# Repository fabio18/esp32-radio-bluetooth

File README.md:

# ESP32 Kindlelaser Max 260W — Metal Cutting Controller

Painel de controle **touch screen** para máquina de corte a laser CO2 **Kindlelaser Max 130W/260W**.
Interface visual industrial com **presets de corte de metal**, monitoramento de segurança e LEDs de status.

## Funcionalidades

- **Controle de potência** PWM (5-99%) com display em Watts
- **Controle de velocidade** de corte (1-80 mm/s)
- **12 presets de material** (Aço Carbono, Inox, Alumínio) com espessuras
- **Monitoramento de segurança**: fluxo de água, tampa, temperatura, E-stop
- **Pulso de teste** para alinhamento do laser
- **Ar comprimido** e **exaustor** controlados pela tela
- **LED WS2812B** para indicação visual de status da máquina
- **Interface touch** — sem botões físicos

## Componentes

| Componente | Descrição |
|---|---|
| **ESP32 DevKit** | Microcontrolador com Wi-Fi (para monitoramento futuro) |
| **ILI9341 TFT 2.4"** | Display 240x320 **com touch XPT2046** |
| **WS2812B** | Fita LED (30 LEDs) para status da máquina |
| **Optoacoplador** | 4N35 ou PC817 — isolamento ESP32 ↔ PSU laser |
| **Conversor de nível** | 3.3V → 5V para sinal PWM |
| **Relé 5V (2ch)** | Para ar comprimido e exaustor |
| **Sensor de fluxo** | Fluxo de água (tipo YF-S201) |
| **NTC 10kΩ** | Sensor de temperatura da água |
| **Botão E-STOP** | Emergência (NC - normalmente fechado) |
| **Chave de tampa** | Microswitch na porta da máquina |

## Layout da Tela Touch

```
┌─────────────────────────────┐
│ KINDLELASER 260W    [STATUS]│  Header
├─────────────────────────────┤
│ MAT: Aco 2.0mm        [O2] │  Preset de material
├─────────────────────────────┤
│   POTENCIA: 95%  (247W)    │  Potência (grande)
│   VELOCIDADE: 12 mm/s      │  Velocidade
├─────────────────────────────┤
│ [POT-] [POT+] [SPD-] [SPD+]│  Controles pot/velocidade
│ [<MAT]  [PULSO]  [MAT>]   │  Material presets
│ [AR]  [EXAUST]  [E-STOP]  │  Auxiliares
│ [═══ LASER ON/OFF ════════]│  Botão principal
├─────────────────────────────┤
│ ████████████████░░░░  95%  │  Barra de potência
├─────────────────────────────┤
│ H2O:OK LID:OK 25°C SEGURO │  Status de segurança
└─────────────────────────────┘
```

## Diagrama de Conexões

### ESP32 → PSU Laser (Kindlelaser Max 260W)

```
ESP32 GPIO 25 (PWM) ──[330Ω]──→ Conversor 3.3V→5V ──→ PSU "IN" (0-5V potência)
ESP32 GPIO 26       ──[1kΩ]──→ Optoacoplador 4N35 ──→ PSU "L-ON" (Laser Enable)
                                 (isolamento galvânico obrigatório!)
```

### ESP32 → Relés de Controle

```
ESP32 GPIO 14  ──→ Relé CH1 ──→ Solenoide ar comprimido (24V)
ESP32 GPIO 12  ──→ Relé CH2 ──→ Exaustor/ventilação (220V)
```

### ESP32 ← Sensores de Segurança

```
Sensor de Fluxo (YF-S201)  ──→ GPIO 33 (INPUT_PULLUP)
Chave de Tampa (NC)         ──→ GPIO 32 (INPUT_PULLUP)
Botão E-STOP (NC)           ──→ GPIO 39 (VN - INPUT)
NTC 10kΩ (divisor)          ──→ GPIO 35 (ADC)
```

### Circuito NTC Temperatura

```
3.3V ──[10kΩ]──┬──[NTC 10kΩ]── GND
               │
               └── GPIO 35 (ADC)
```

### ILI9341 TFT + Touch → ESP32 (SPI)

```
ILI9341      ESP32         Função
───────      ─────         ──────
MOSI   ───── GPIO 23       SPI Data (compartilhado)
MISO   ───── GPIO 19       SPI Data (compartilhado)
SCK    ───── GPIO 18       SPI Clock (compartilhado)
CS     ───── GPIO 15       Chip Select Display
DC     ───── GPIO  2       Data/Command
RST    ───── GPIO  4       Reset
LED    ───── 3.3V          Backlight
T_CS   ───── GPIO 27       Chip Select Touch
T_IRQ  ───── GPIO 34       Touch Interrupt (opcional)
VCC    ───── 3.3V
GND    ───── GND
```

### WS2812B LED Strip

```
WS2812B      ESP32
───────      ─────
DIN    ───── GPIO 13       Data (com resistor 330Ω)
VCC    ───── 5V            Fonte externa
GND    ───── GND           Compartilhado
```

### Diagrama Completo

```
                    ┌─────────────────────┐
                    │     ESP32 DevKit     │
                    │                     │
  PSU Laser ──PWM──┤ GPIO25 (PWM)        │── 20kHz → 0-5V potência
  (Kindlelaser)     │ GPIO26 (ENABLE)     │── Optoacoplador → L-ON
                    │                     │
  ILI9341 ───SPI──┤ GPIO23 (MOSI)       │── compartilhado
  (Display)        │ GPIO19 (MISO)       │── com touch
                   │ GPIO18 (SCK)        │── XPT2046
                   │ GPIO15 (CS Display) │
                   │ GPIO2  (DC)         │
                   │ GPIO4  (RST)        │
                   │                     │
  XPT2046 ────────┤ GPIO27 (CS Touch)   │
  (Touch)          │                     │
                   │                     │
  Ar Comprimido ──┤ GPIO14 (Relé)       │── Solenoide 24V
  Exaustor ───────┤ GPIO12 (Relé)       │── Ventilação 220V
                   │                     │
  WS2812B ────────┤ GPIO13 (LED Data)   │
  (Status LEDs)    │                     │
                   │                     │
  Sensor Fluxo  ──┤ GPIO33 (INPUT)      │── Água OK?
  Chave Tampa  ───┤ GPIO32 (INPUT)      │── Tampa fechada?
  E-STOP  ────────┤ GPIO39 (INPUT)      │── Emergência?
  NTC Temp  ──ADC─┤ GPIO35 (ADC)        │── Temperatura água
                   │                     │
                   └─────────────────────┘
```

---

## Presets de Corte de Metal (Kindlelaser 260W)

| # | Material | Espessura | Potência | Velocidade | Gás |
|---|---|---|---|---|---|
| 1 | Aço Carbono | 0.5mm | 70% | 30 mm/s | O₂ |
| 2 | Aço Carbono | 1.0mm | 85% | 20 mm/s | O₂ |
| 3 | Aço Carbono | 1.5mm | 92% | 15 mm/s | O₂ |
| 4 | Aço Carbono | 2.0mm | 95% | 12 mm/s | O₂ |
| 5 | Aço Carbono | 3.0mm | 99% | 8 mm/s | O₂ |
| 6 | Inox | 0.5mm | 75% | 25 mm/s | N₂ |
| 7 | Inox | 1.0mm | 90% | 15 mm/s | N₂ |
| 8 | Inox | 1.5mm | 95% | 10 mm/s | N₂ |
| 9 | Inox | 2.0mm | 99% | 6 mm/s | N₂ |
| 10 | Alumínio | 0.5mm | 80% | 20 mm/s | N₂ |
| 11 | Alumínio | 1.0mm | 92% | 12 mm/s | N₂ |
| 12 | Alumínio | 1.5mm | 99% | 7 mm/s | N₂ |

> **Nota:** Estes valores são pontos de partida. Ajuste conforme o estado do tubo, lente e condições do material. A Kindlelaser 130W corta até ~2mm de aço; a 260W até ~3mm.

---

## Sistema de Segurança

O sistema implementa **4 camadas de segurança**:

| Sensor | Condição para operar | Ação se falhar |
|---|---|---|
| **Fluxo de água** | Sensor detecta fluxo (LOW) | Desliga laser imediatamente |
| **Tampa** | Microswitch fechado (LOW) | Desliga laser imediatamente |
| **E-STOP** | Botão não pressionado (HIGH) | Desliga TUDO (emergency stop) |
| **Temperatura** | < 35°C | Desliga laser + aviso |

Adicionalmente:
- **Tempo máximo de corte contínuo**: 5 minutos → pausa obrigatória
- **Potência máxima limitada**: 99% (protege vida útil do tubo)
- **Ar comprimido obrigatório**: não pode ser desligado durante corte
- **Exaustor automático**: liga junto com o laser

---

## Indicação LED (WS2812B)

| Status | Efeito LED | Significado |
|---|---|---|
| **IDLE** | Azul pulsante (respiração) | Máquina em espera |
| **PRONTO** | Verde fixo | Segurança OK, pronto para cortar |
| **CORTANDO** | Vermelho pulsante rápido | Laser ativo! |
| **AVISO** | Amarelo piscante | Temperatura alta ou pausa |
| **ERRO** | Vermelho piscante | Falha de segurança |
| **RESFRIANDO** | Azul gradiente | Aguardando resfriamento |

---

## Como Compilar e Gravar

### PlatformIO (recomendado)

```bash
# Compilar
pio run

# Gravar no ESP32
pio run --target upload

# Monitor Serial
pio device monitor
```

### Arduino IDE

1. Instale o suporte ESP32 (URL: `https://raw.githubusercontent.com/espressif/arduino-esp32/gh-pages/package_esp32_index.json`)
2. Instale bibliotecas: **TFT_eSPI**, **FastLED**
3. Copie `arduino/esp32_radio_bluetooth/User_Setup.h` para a pasta do TFT_eSPI
4. Configure: ESP32 Dev Module, Huge APP (3MB), 921600 baud
5. Upload

---

## Como Usar

### Primeiro Boot

1. Tela splash "KINDLELASER MAX 260W"
2. Verifica condições de segurança
3. Se tudo OK → status "PRONTO" (LED verde)

### Controles Touch

| Botão | Função |
|---|---|
| **POT-** / **POT+** | Diminuir/aumentar potência (±5%) |
| **SPD-** / **SPD+** | Diminuir/aumentar velocidade (±1 mm/s) |
| **<MAT** / **MAT>** | Trocar preset de material |
| **PULSO** | Disparo de teste (100ms) para alinhamento |
| **AR** | Liga/desliga ar comprimido |
| **EXAUST** | Liga/desliga exaustor |
| **E-STOP** | Parada de emergência (software) |
| **LASER ON/OFF** | Liga/desliga o laser |

### Sequência de Operação

1. Ligue a máquina → ESP32 faz checagem de segurança
2. Aguarde LED verde (PRONTO)
3. Selecione o material com **<MAT / MAT>**
4. Ajuste potência e velocidade se necessário
5. Use **PULSO** para verificar alinhamento
6. Toque **LASER ON/OFF** para iniciar corte
7. LED fica vermelho pulsante durante corte
8. Toque novamente para desligar

---

## Estrutura do Projeto

```
esp32-radio-bluetooth/
├── platformio.ini              # Configuração PlatformIO
├── include/
│   ├── config.h                # Pinos, presets, segurança, cores
│   ├── display_ui.h            # Interface touch industrial
│   ├── laser_control.h         # Controle do laser + segurança
│   └── led_effects.h           # LED status strip
├── src/
│   ├── main.cpp                # Firmware principal
│   ├── display_ui.cpp          # UI industrial + touch
│   ├── laser_control.cpp       # PWM + safety + presets
│   └── led_effects.cpp         # Efeitos LED de status
├── docs/
│   └── wiring.md               # Conexões detalhadas
└── arduino/
    └── esp32_radio_bluetooth/
        └── User_Setup.h        # Config TFT_eSPI
```

## Dependências

| Biblioteca | Versão | Uso |
|---|---|---|
| [TFT_eSPI](https://github.com/Bodmer/TFT_eSPI) | ^2.5.34 | Display ILI9341 + Touch XPT2046 |
| [FastLED](https://github.com/FastLED/FastLED) | ^3.6.0 | WS2812B LED status strip |

## Customização

### Alterar presets de corte
Em `include/config.h`, modifique o array `CUTTING_PRESETS[]`:
```cpp
{"Aco 4.0mm", 99, 5, true, "O2", 4.0f},
```

### Alterar limites de segurança
```cpp
#define WATER_TEMP_MAX      35.0f   // Temperatura máxima (°C)
#define MAX_CONTINUOUS_CUT  300000  // Tempo máximo corte (ms)
#define POWER_MAX           99      // Potência máxima (%)
```

### Alterar PWM
```cpp
#define LASER_PWM_FREQ      20000   // Frequência (Hz)
#define LASER_PWM_RESOLUTION 12     // Resolução (bits)
```

---

## ⚠️ AVISOS DE SEGURANÇA

1. **SEMPRE use óculos de proteção** adequados para CO2 (OD5+ @ 10.6µm)
2. **NUNCA opere sem fluxo de água** — o tubo CO2 queima em segundos
3. **Use optoacopladores** entre ESP32 e PSU laser (isolamento galvânico)
4. **O botão E-STOP físico deve funcionar INDEPENDENTE do ESP32** — cabeie diretamente na PSU como segurança adicional
5. **Ventilação obrigatória** — fumos metálicos são tóxicos
6. **Este painel é AUXILIAR** — não substitui o controlador principal (Ruida) para movimentação dos eixos

---

## Comunicação com Ruida (Opcional)

O ESP32 pode se comunicar via UART com a controladora Ruida RDC6445/6442:
- GPIO 16 (RX) ← Ruida TX
- GPIO 17 (TX) → Ruida RX
- Baud: 115200

Isso permite receber feedback de posição e status da controladora principal.

## Licença

MIT License

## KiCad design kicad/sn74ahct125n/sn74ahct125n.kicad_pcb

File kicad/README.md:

# PCB Level Shifter — ESP32 + SN74HCT125 + WS2812B

Placa de circuito impresso para converter o sinal de 3.3V do ESP32 para 5V compativel com os LEDs WS2812B, usando o CI **SN74HCT125** (Quad Buffer/Line Driver com saidas 3-state).

## Esquema do Circuito

```
                         SN74HCT125 (U1)
                         DIP-14
                    ┌──────────────────┐
  GND ──────────────┤ 1  ~1OE    VCC 14├──── +5V
                    │                   │
  ESP32 GPIO13 ─────┤ 2  1A      ~4OE13├──── GND
                    │                   │
             ┌──────┤ 3  1Y       4A  12├
             │      │                   │
  GND ──────────────┤ 4  ~2OE    4Y  11├
             │      │                   │
             │      ┤ 5  2A      ~3OE10├──── GND
             │      │                   │
             │      ┤ 6  2Y       3A   9├
             │      │                   │
             │      ┤ 7  GND      3Y   8├
             │      └──────────────────┘
             │           │  ││  │
             │          GND ││ +5V
             │           100nF
             │
          [62-100R]
             │
        WS2812B DIN
```

## Por que SN74HCT125?

O ESP32 opera com logica de **3.3V**, mas os LEDs WS2812B precisam de sinais de **5V**.
O SN74HCT125 e um quad buffer com entradas compativeis TTL — aceita **3.3V como nivel HIGH** e produz saida em **5V**.

- **~1OE = GND**: Saida do canal 1 habilitada (active low)
- **~2OE, ~3OE, ~4OE = GND**: Todas as saidas habilitadas
- **1A (pino 2)**: Entrada de dados do GPIO13 do ESP32 (3.3V)
- **1Y (pino 3)**: Saida de dados em 5V → resistor → WS2812B DIN
- **VCC (pino 14) = +5V**: Alimentacao do CI
- **GND (pino 7) = GND**

### Vantagens do SN74HCT125

- Mais simples que o SN74HCT245 (14 pinos vs 20 pinos)
- Saidas independentes com controle individual via ~OE
- Buffer unidirecional (ideal para dados do LED — sempre ESP32 → WS2812B)
- Mesmo principio TTL — aceita 3.3V como HIGH na entrada

## Conectores

| Conector | Pinos | Funcao |
|----------|-------|--------|
| **J1** (ESP32) | 1: GPIO13, 2: 3.3V, 3: 5V, 4: GND | Conexao com ESP32 DevKit |
| **J2** (WS2812B) | 1: DIN, 2: VCC (5V), 3: GND | Saida para fita LED |
| **J3** (Alimentacao) | 1: +5V, 2: GND | Entrada de alimentacao externa |

## Lista de Materiais (BOM)

| Ref | Componente | Valor | Footprint | Qtd |
|-----|-----------|-------|-----------|-----|
| U1 | SN74HCT125N | - | DIP-14 (7.62mm) | 1 |
| R1 | Resistor | 62-100R | Axial | 1 |
| C1 | Capacitor ceramico | 100nF | Disco 5mm | 1 |
| C2 | Capacitor eletrolitico | 1000uF/10V | Radial 8mm | 1 |
| J1 | Barra de pinos | 1x4 | 2.54mm | 1 |
| J2 | Barra de pinos | 1x3 | 2.54mm | 1 |
| J3 | Barra de pinos | 1x2 | 2.54mm | 1 |

## Dimensoes da Placa

- **Tamanho**: 40mm x 30mm
- **Camadas**: 2 (F.Cu + B.Cu)
- **Furos de montagem**: 4x nos cantos (M3)

## Como Usar

### Requisitos
- [KiCad 10](https://www.kicad.org/) ou superior

### Abrir o Projeto
1. Abra o KiCad
2. **Arquivo → Abrir Projeto**
3. Navegue ate `kicad/esp32_ws2812b_levelshifter/`
4. Selecione `esp32_ws2812b_levelshifter.kicad_pro`

### Fluxo de Trabalho
1. Abra o esquematico e verifique as conexoes
2. Rode o ERC (Electrical Rules Check)
3. Atribua/verifique os footprints
4. Abra o editor de PCB e posicione os componentes
5. Roteie as trilhas
6. Rode o DRC (Design Rule Check)
7. Gere os arquivos Gerber para fabricacao

## Diagrama de Conexao com o Projeto ESP32 Radio

```
ESP32 DevKit                Level Shifter PCB          WS2812B LED Strip
┌──────────┐               ┌─────────────────┐        ┌──────────────┐
│          │               │ J1          J2  │        │              │
│  GPIO13 ─┼───────────────┤─1 SN74HCT125  1├────────┤─ DIN         │
│    3.3V ─┼───────────────┤─2              2├────────┤─ VCC (5V)    │
│      5V ─┼───────────────┤─3              3├────────┤─ GND         │
│     GND ─┼───────────────┤─4               │        │              │
│          │               │                 │        └──────────────┘
└──────────┘               │ J3 (Fonte 5V)   │
                           │  1: +5V         │
Fonte 5V/2A ───────────────┤  2: GND         │
                           └─────────────────┘
```

## Notas Importantes

1. **Alimentacao**: Use fonte 5V externa com capacidade minima de 2A para 30 LEDs WS2812B
2. **Capacitor C1 (100nF)**: Posicione proximo aos pinos VCC/GND do SN74HCT125
3. **Capacitor C2 (1000uF)**: Posicione proximo ao conector J2 (WS2812B) para filtrar picos
4. **Resistor R1 (62-100R)**: Protege o pino DIN do WS2812B contra reflexoes de sinal
5. **Canais extras**: Pinos 2A/2Y, 3A/3Y, 4A/4Y estao disponiveis para uso futuro
6. **GND compartilhado**: ESP32, level shifter e WS2812B devem compartilhar o mesmo GND
7. **~OE pinos**: Todos conectados ao GND para manter as saidas sempre habilitadas

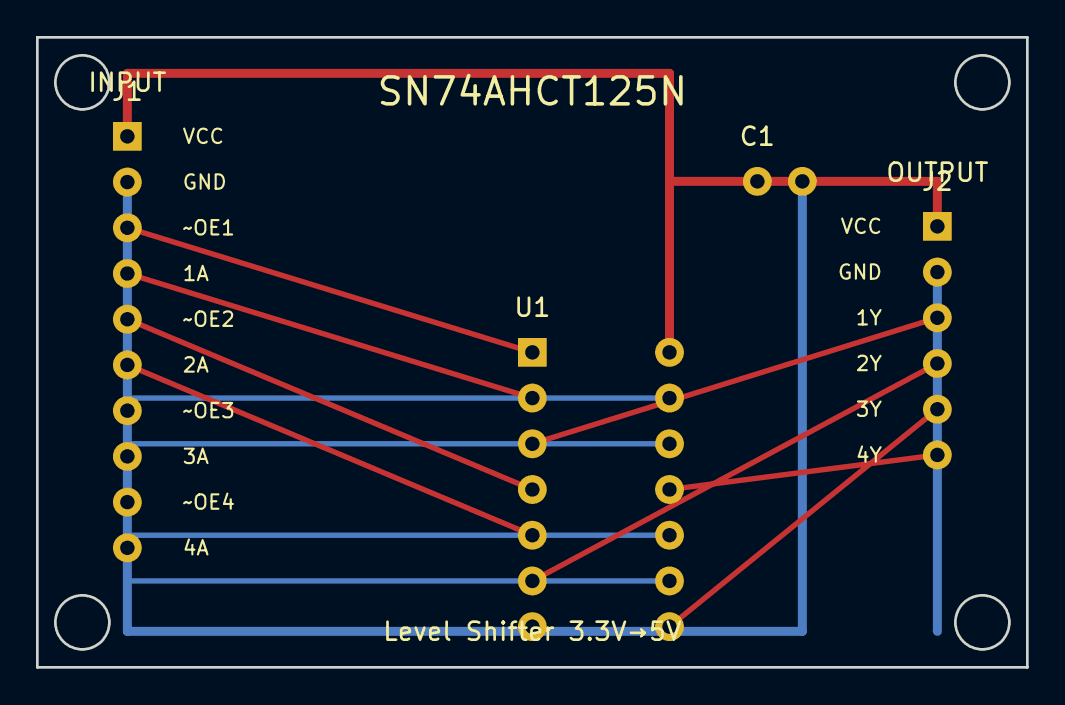
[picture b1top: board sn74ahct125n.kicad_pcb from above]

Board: 2 copper layers, 55.0 x 35.0 mm, 4 parts (0 on the bottom side), 14 nets.

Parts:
C1: 100nF; C_Disc_D5.0mm_W2.5mm_P2.50mm
J1: INPUT; PinHeader_1x10_P2.54mm_Vertical
J2: OUTPUT; PinHeader_1x06_P2.54mm_Vertical
U1: SN74AHCT125N; DIP-14_W7.62mm

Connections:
A1: J1.4, U1.2
A2: J1.6, U1.5
A3: J1.8, U1.9
A4: J1.10, U1.12
GND: C1.2, J1.2, J2.2, U1.7
OE1: J1.3, U1.1
OE2: J1.5, U1.4
OE3: J1.7, U1.10
OE4: J1.9, U1.13
VCC: C1.1, J1.1, J2.1, U1.14
Y1: J2.3, U1.3
Y2: J2.4, U1.6
Y3: J2.5, U1.8
Y4: J2.6, U1.11

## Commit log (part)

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2026-04-24 feat: ESP32 Radio Bluetooth com Alexa - firmware completo
    Componentes suportados:
    - ESP32 DevKit (Bluetooth + Wi-Fi)
    - TEA5767 Módulo FM Estéreo (76-108 MHz)
    - Display TFT ILI9341 2.4" 240x320
    Funcionalidades:
    - Modo FM: sintonização, busca automática, presets
2026-04-25 feat: Pioneer-style UI + WS2812B LED reativo ao som + touch control
    - Visual estilo Pioneer automotivo com cores neon cyan/blue
    - Tela splash com logo e barra de loading estilo Pioneer
    - Frequência grande com efeito glow e equalizador animado
    - Botões touch com bordas luminosas estilo automotivo
    - WS2812B LED strip com 5 efeitos reativos ao áudio:
    VU Meter, Spectrum, Pulse, Rainbow, Fire
2026-04-25 feat: add Arduino IDE version + setup instructions
    - Single .ino file with all code (TEA5767, BT, Display, LED effects)
    - User_Setup.h for TFT_eSPI library configuration
    - Step-by-step Arduino IDE instructions in README
    - Board settings: ESP32 Dev Module, Huge APP partition
2026-04-26 fix: Arduino IDE compilation errors (ESP32 core 3.x)
    - Replace legacy i2s_pin_config_t/set_pin_config with AudioTools I2SStream
    - Rename btStarted to btActive (conflicts with esp32-hal-bt.h function)
    - Add arduino-audio-tools dependency (required for ESP32 3.x I2S API)
    - Update README with new library requirement
2026-05-03 feat: add KiCad 10 PCB project - ESP32 + SN74HCT245 level shifter for WS2812B
    - Schematic with SN74HCT245 as 3.3V to 5V level shifter
    - ESP32 GPIO13 -> A1 -> B1 -> 330R -> WS2812B DIN
    - DIR=HIGH (A->B), OE=LOW (outputs enabled)
    - Bypass capacitors (100nF) near VCC pins
    - 1000uF bulk capacitor for WS2812B power filtering
    - Connectors: J1 (ESP32), J2 (WS2812B), J3 (5V power input)
2026-05-03 refactor: update to SN74HCT125 (DIP-14) per user schematic
    - Replace SN74HCT245 (DIP-20) with SN74HCT125 (DIP-14, quad buffer)
    - All ~OE pins tied to GND (outputs always enabled)
    - Channel 1: GPIO13 -> 1A (pin2) -> 1Y (pin3) -> R1 -> WS2812B DIN
    - Resistor changed from 330R to 62-100R per reference schematic
    - 100nF bypass cap between VCC (pin14) and GND (pin7)
    - PCB reduced to 40x30mm (smaller IC footprint)
2026-05-03 fix: use official KiCad multi-unit symbol format for SN74HCT125
    - Symbol now uses 5 units (4 gates + power) matching KiCad 74xx library format
    - Each gate drawn as triangle buffer with ~OE, A input, Y output
    - Unit 5 contains VCC (pin 14) and GND (pin 7) in rectangle
    - Fixes symbol loading issue in KiCad 10
    - Matches official 74LS125 symbol structure (74HCT125 extends 74LS125)
2026-05-03 fix: single-unit DIP-14 block symbol for SN74HCT125
    - All 14 pins visible in one rectangle block (DIP-14 layout)
    - Left side: pins 1-7 (~1OE, 1A, 1Y, ~2OE, 2A, 2Y, GND)
    - Right side: pins 14-8 (VCC, ~4OE, 4A, 4Y, ~3OE, 3A, 3Y)
    - Pin names with overbar notation: ~{1OE}, ~{2OE}, ~{3OE}, ~{4OE}
    - IC shows as complete DIP-14 package in schematic
2026-05-03 feat: add KiCad PCB project for SN74AHCT125N level shifter
    - Complete KiCad project with schematic and PCB layout
    - Custom symbol library for SN74AHCT125N (DIP-14)
    - Footprint libraries: DIP-14, capacitor, pin headers
    - PCB breakout board (55x35mm) with:
    - U1: SN74AHCT125N quadruple bus buffer
    - C1: 100nF bypass capacitor
